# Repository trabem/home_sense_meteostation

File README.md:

# Автономна метеостанція на ESP32-C3

Репозиторій автономної battery-powered метеостанції на **ESP32-C3-WROOM-02**.
Містить firmware (ESP-IDF / FreeRTOS), KiCad-проєкти двох плат і матеріали
фінальної презентації.

Принцип роботи на battery: **wake → визначити причину → прочитати потрібні
дані → передати → перевести периферію в low-power → deep sleep**.

## Що вимірює і передає

- температура, тиск, вологість — **BME280**;
- напруга, струм, потужність battery і solar — **INA226 ×2**;
- час — RTC **DS3231** (CR2032 backup);
- стан зарядки (TP5000) і вибір транспорту — **PCA9536**;
- події блискавки — **AS3935** через `WAKE_IRQ` з негайною передачею
  distance/energy.

Транспорт вибирається перемикачем **J4**:

| J4 | Режим |
| -- | ----- |
| open / HIGH | **LoRa** (SX1262 / E22-900M22S, TX-only, компактний binary payload) — energy-safe default |
| closed / LOW | **Wi-Fi + MQTT** (JSON, `mqtts://`, BLE provisioning за відсутності credentials) |

Підключення USB автоматично вмикає continuous mode — цикли за таймером без
deep sleep, порт лишається живим для прошивки й монітору.

## Структура репозиторію

```text
software/       firmware: C11+, ESP-IDF v6.0.1, FreeRTOS, target esp32c3
  main/         composition root (app_main, flows, app_config)
  components/   board, app_flow, power_manager, sensor_manager,
                lightning_service, драйвери (bme280, as3935, ina226, ds3231,
                pca9536, sx1262), transport (MQTT/LoRa), telemetry, ...
  docs/         Mermaid-діаграми call flow і модулів
hardware/
  main_board/   KiCad-проєкт основної плати (MCU, LoRa, power: USB/Solar/1S LiFePO4)
  sensor_board/ KiCad-проєкт плати датчиків (BME280 + CJMCU-3935/AS3935)
presentation/   фінальна презентація (PDF/PPTX) і генератор
AGENTS.md       правила проєкту для AI-агентів і контрибуторів
TZ.md           історичне implementation specification
```

## Швидкий старт (firmware)

Потрібне activated ESP-IDF **v6.0.1** environment (`IDF_PATH`, `idf.py`):

```bash
cd software
idf.py set-target esp32c3   # тільки для clean setup
idf.py menuconfig           # меню "Meteostation"
idf.py build
idf.py -p PORT flash
idf.py -p PORT monitor
```

Деталі — у [`software/README.md`](software/README.md): pin mapping, I2C
addresses, MQTT/LoRa конфігурація, BLE provisioning, deep sleep і power
behavior.

## Hardware

Два KiCad-проєкти (generator_version 10.0):

- **main_board** — ESP32-C3, E22-900M22S (SX1262), power mux TPS2121
  (USB-over-Solar priority), зарядний контролер TP5000 для 1S LiFePO4,
  buck-boost 3.3 V, INA226 ×2, DS3231, PCA9536;
- **sensor_board** — BME280 (0x76) + AS3935 (0x03), підключення до основної
  плати через I²C і `WAKE_IRQ`.

Очікувані I2C addresses: `0x40` solar INA226, `0x41` PCA9536, `0x44` battery
INA226, `0x68` DS3231, `0x03` AS3935, `0x76` BME280.

## Поза скоупом V1

OTA, HTTP/web UI, LoRaWAN/RX/ACK, persistent telemetry queue, FRAM, SD card,
backend, remote configuration — навмисно не реалізовані.

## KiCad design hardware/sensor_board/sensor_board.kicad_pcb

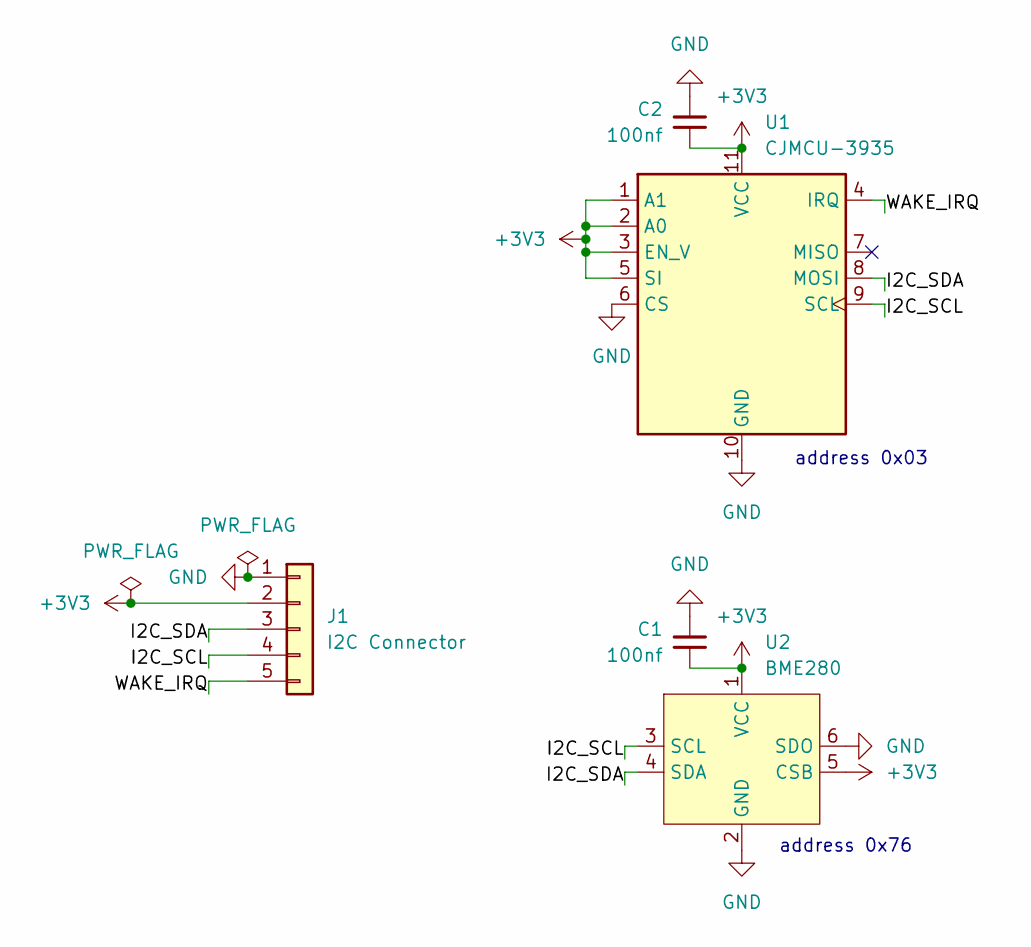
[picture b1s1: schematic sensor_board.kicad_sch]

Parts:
C1, C2: 100nf; C_Disc_D5.0mm_W2.5mm_P2.50mm
J1: I2C Connector; JST_PH_B5B-PH-K_1x05_P2.00mm_Vertical
U1: CJMCU-3935
U2: BME280; BME280 Module

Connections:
+3V3: C1.2, C2.2, J1.2, U1.1 (A1), U1.2 (A0), U1.3 (EN_V), U1.5 (SI), U1.11 (VCC), U2.1 (VCC), U2.5 (CSB)
/I2C_SCL: J1.4, U1.9 (SCL), U2.3 (SCL)
/I2C_SDA: J1.3, U1.8 (MOSI), U2.4 (SDA)
/WAKE_IRQ: J1.5, U1.4 (IRQ)
GND: C1.1, C2.1, J1.1, U1.6 (CS), U1.10 (GND), U2.2 (GND), U2.6 (SDO)

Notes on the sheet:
address 0x76
address 0x03

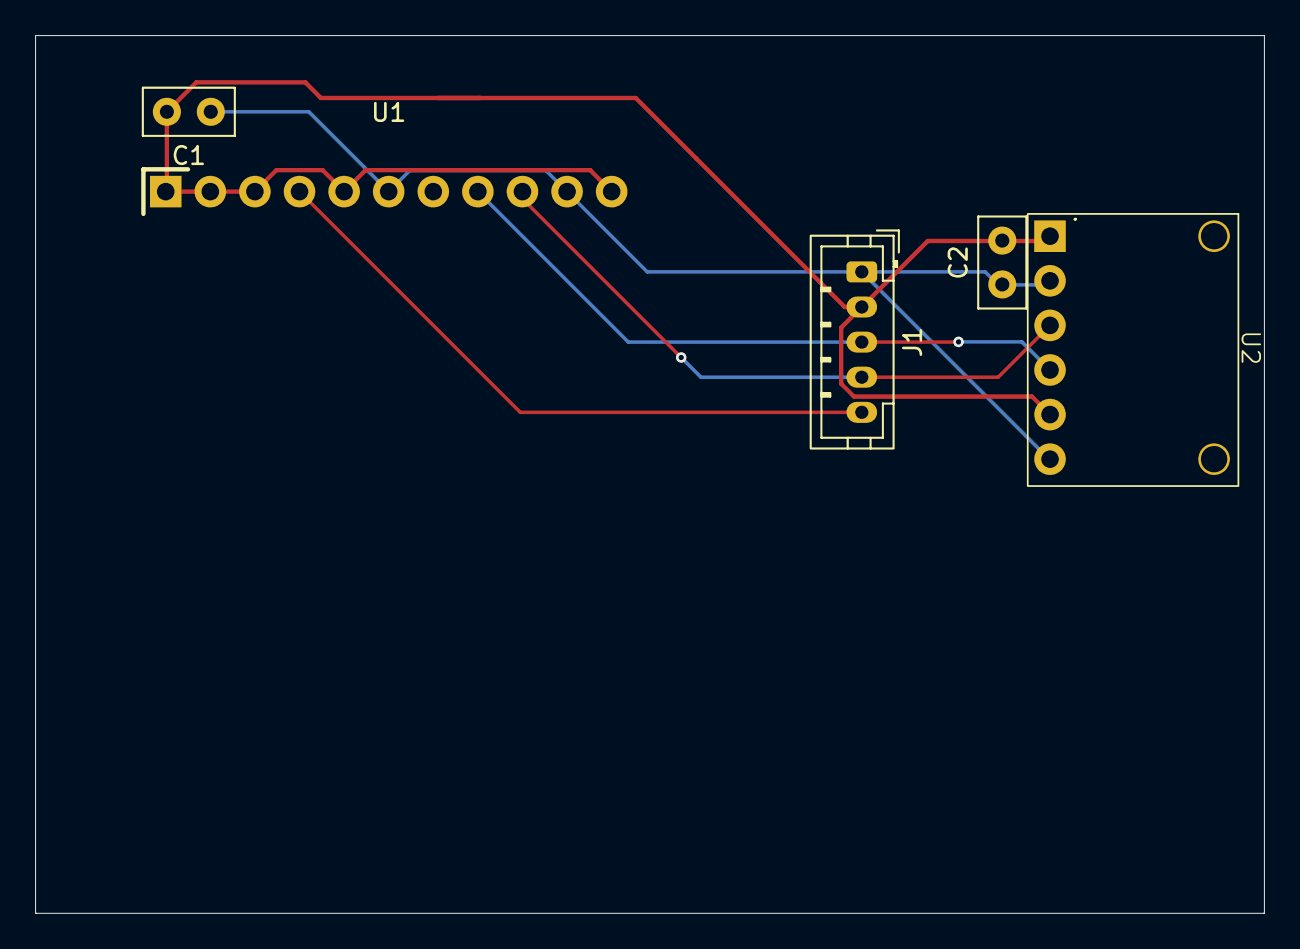
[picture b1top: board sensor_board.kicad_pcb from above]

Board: 2 copper layers, 70.0 x 50.0 mm, 5 parts (0 on the bottom side), 5 nets.

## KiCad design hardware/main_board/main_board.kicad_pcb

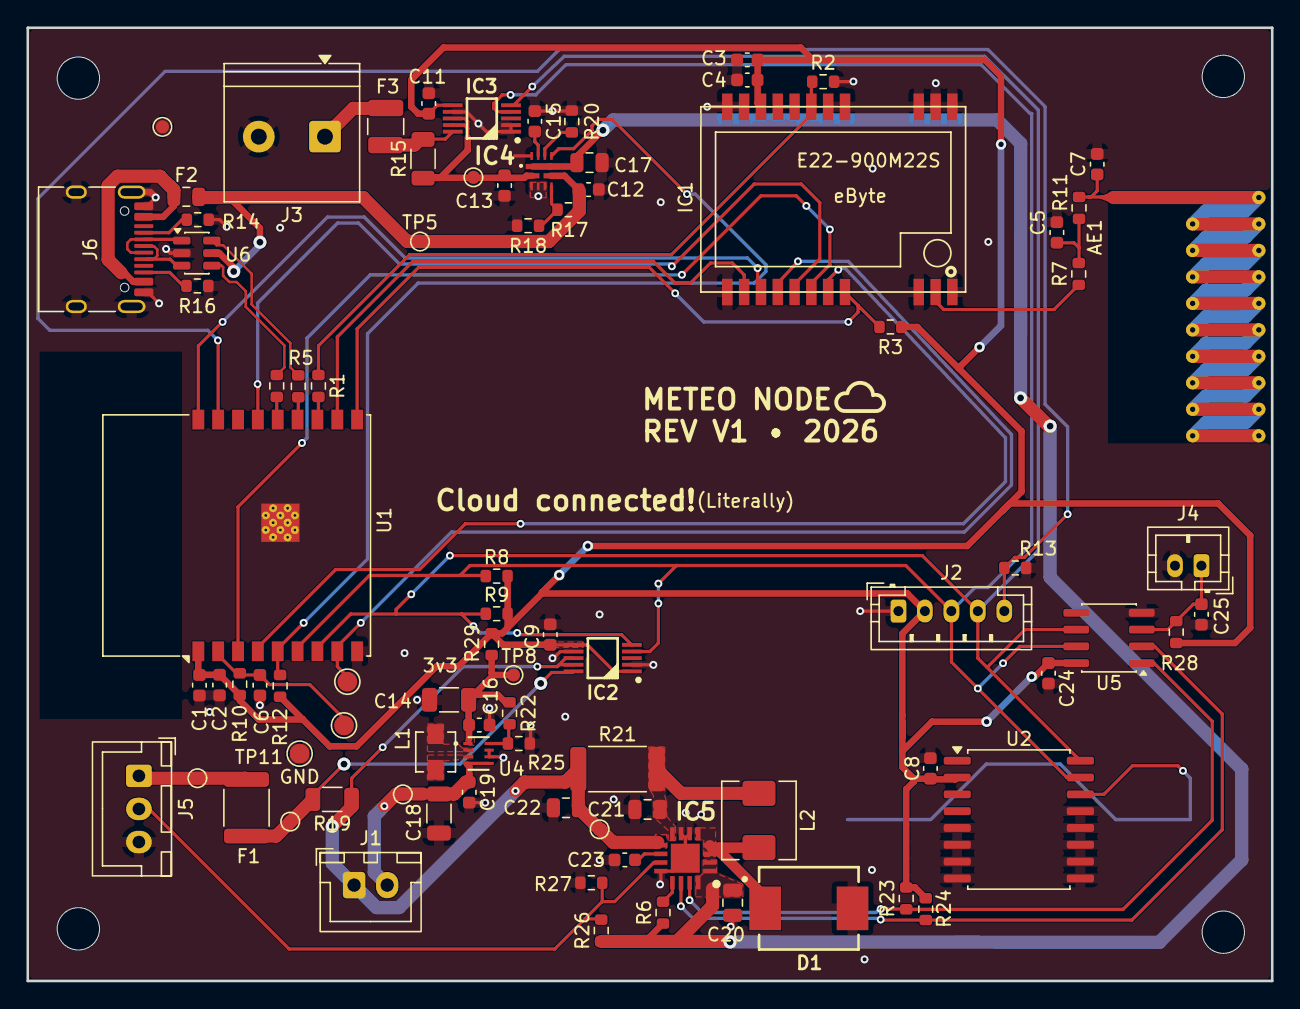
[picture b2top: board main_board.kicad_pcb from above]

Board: 2 copper layers, 94.0 x 72.0 mm, 92 parts (1 on the bottom side), 54 nets.

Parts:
AE1: Antenna; Texas_SWRA416_868MHz_915MHz
BT1: CR2032; BatteryHolder_Multicomp_BC-2001_1x2032
C1, C4: 10uF; C_0603_1608Metric
C2, C3, C8, C9, C11, C15, C16, C19, C23, C24, C25: 100nF; C_0603_1608Metric
C5, C7: DNP; C_0603_1608Metric
C6, C12, C13: 1uF; C_0603_1608Metric
C14: 47uF; C_1206_3216Metric
C17: 4.7uF; C_0805_2012Metric
C18: 22uF; C_1206_3216Metric
C20, C21, C22: 10uF; C_0805_2012Metric
D1: SS34; DO-214AB
F1: MINISMDC200F-2; Fuse_1812_4532Metric
F2: 0ZCK0075FF2E; Fuse_0805_2012Metric
F3: 0ZCH0075AF2E; Fuse_1210_3225Metric
IC1: E22-900M22S
IC2, IC3: INA226AIDGST; SOP50P490X110-10N
IC4: TPS2121RUXT
IC5: TP5000-QFN16; QFN65P400X400X90-17N-D
J1: power swith; JST_XH_B2B-XH-A_1x02_P2.50mm_Vertical
J2: I2C External Modules; JST_PH_B5B-PH-K_1x05_P2.00mm_Vertical
J3: Solar panel; TerminalBlock_Philmore_TB132_1x02_P5.00mm_Horizontal
J4: WI-FI switch; JST_PH_B2B-PH-K_1x02_P2.00mm_Vertical
J5: Battary over BMS; JST_XH_B3B-XH-A_1x03_P2.50mm_Vertical
J6: USB4105-GF-A-060; USB_C_Receptacle_HRO_TYPE-C-31-M-12
L1: IHLP1212BZER1R0M11; IND_IHLP1212BZER1R0M11
L2: 4.7 uH; L_Chilisin_BMRA00050520
R1, R6, R7, R11, R29: 0R; R_0603_1608Metric
R2, R3, R10, R12, R23, R24: 10k; R_0603_1608Metric
R4, R5: 22R; R_0603_1608Metric
R8, R9: 4.7k; R_0603_1608Metric
R13, R18, R28: 47k; R_0603_1608Metric
R14, R16: 5.1k; R_0603_1608Metric
R15, R19: 20mR; R_1206_3216Metric
R17: 150k; R_0603_1608Metric
R20: 80k; R_0603_1608Metric
R21: 330mR; R_2512_6332Metric
R22: 511k; R_0603_1608Metric
R25: 91k; R_0603_1608Metric
R26: 4.87k; R_0603_1608Metric
R27: 44.2k; R_0603_1608Metric
REF1, REF2, REF3, REF4: MountingHole_3.2mm_M3
TP1: TP_SOLAR_IN; TestPoint_Pad_D1.0mm
TP2: TP_BAT_RAW; TestPoint_Pad_D1.0mm
TP3: TP_BAT_FUSED; TestPoint_Pad_D1.0mm
TP4: TP_BAT_SYSTEM; TestPoint_Pad_D1.0mm
TP5: TP_USB_5V; TestPoint_Pad_D1.0mm
TP6: ESP32_EN; TestPoint_Pad_D1.5mm
TP7: TP_BAT_SW; TestPoint_Pad_D1.0mm
TP8: TP_3V3; TestPoint_Pad_D1.0mm
TP9: TP_GND_PWR; TestPoint_Pad_D1.0mm
TP10: ESP32_BOOT; TestPoint_Pad_D1.5mm
TP11: GND; TestPoint_Pad_D1.5mm
U1: ESP32-C3-WROOM-02
U2: DS3231SN; SOIC-16W_7.5x10.3mm_P1.27mm
U4: TPS631000DRLR; TPS631000DRLR_TEX
U5: PCA9536DR; SOIC-8_3.9x4.9mm_P1.27mm
U6: USBLC6-2SC6; SOT-23-6

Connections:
+3V3: C1.1, C2.1, C3.2, C4.1, C8.2, C9.2, C11.2, C24.1, IC1.9 (VCC), IC2.1 (A1), IC2.6 (VS+), IC3.6 (VS+), J2.2, R3.2, R8.2, R9.2, R10.1, R12.2, R23.2, R24.2, R28.1, R29.2, U1.1 (3V3), U2.2 (VCC), U5.8 (VDD)
/Power/BAT_RAW: F1.1, J5.1, TP2.1 (1_1)
/Power/CHARGER_IN: C17.2, C20.1, IC4.1 (OUT_1), IC4.8 (OUT_2), IC5.1 (VIN_1), IC5.2 (VIN_2), IC5.16 (VIN_3), R6.1, R26.1
/Power/LX_SW: D1.1 (K), IC5.3 (LX_1), IC5.4 (LX_2), IC5.5 (LX_3), L2.1
/Power/NTC_SENSE: IC5.11 (TS), J5.2, R26.2, R27.1
/Power/USB_5V: C12.2, F2.2, IC4.7 (IN1), R17.2, TP5.1 (1_1), U6.5 (VBUS)
/main_board/I2C_SCL: IC2.5 (SCL), IC3.5 (SCL), J2.4, R9.1, U1.7 (IO8), U2.16 (SCL), U5.6 (SCL)
/main_board/I2C_SDA: IC2.4 (SDA), IC3.4 (SDA), J2.3, R8.1, U1.6 (IO7), U2.15 (SDA), U5.7 (SDA)
/main_board/LORA_BUSY: IC1.14 (BUSY), U1.18 (IO0)
/main_board/LORA_DIO1: IC1.13 (DIO1), U1.11 (IO20/RXD)
/main_board/LORA_NRST: IC1.15 (NRST), TP10.1 (1_1), U1.8 (IO9)
/main_board/LORA_NSS: IC1.19 (NSS), R3.1, U1.10 (IO10)
/main_board/LORA_RXEN: IC1.6 (RXEN), R1.1, R2.1
/main_board/LORA_TXEN: IC1.7 (TXEN), IC1.8 (DIO2)
/main_board/SPI_MISO: IC1.16 (MISO), U1.15 (IO3)
/main_board/SPI_MOSI: IC1.17 (MOSI), U1.3 (IO4)
/main_board/SPI_SCK: IC1.18 (SCK), U1.4 (IO5)
/main_board/WAKE_IRQ: J2.5, R13.1, U1.17 (IO1)
/main_board/WIFI_SW: C25.2, J4.1, R28.2, U5.3 (IO2)
BAT_FUSED: F1.2, IC2.10 (VIN+), R19.2, TP3.1 (1_1)
BAT_SW: C22.1, IC2.8 (VBUS), IC2.9 (VIN-), IC5.9 (BAT), J1.1, R19.1, R21.1, TP7.1 (1_1)
BAT_SYSTEM: C18.1, C19.1, J1.2, TP4.1 (1_1), U4.4 (VIN), U4.5 (EN)
BT_CR2032: BT1.1 (+), U2.14 (VBAT)
CHARGE_SOURCE_STATUS_OUT: IC4.9 (ST), R12.1, U1.5 (IO6)
CHRG_STATUS: IC5.15 (~CHRG), R23.1, U5.1 (IO0)
GND: BT1.2 (-), C1.2, C2.2, C3.1, C4.2, C5.2, C6.2, C7.2, C8.1, C9.1, C11.1, C12.1, C13.1, C14.2, C15.1, C16.2, C17.1, C18.2, C19.2, C20.2, C21.2, C22.2, C23.2, C24.2, C25.1, D1.2 (A), IC1.1 (GND), IC1.2 (GND), IC1.3 (GND), IC1.4 (GND), IC1.5 (GND), IC1.10 (GND), IC1.11 (GND), IC1.12 (GND), IC1.20 (GND), IC1.22 (GND), IC2.2 (A0), IC2.7 (GND), IC3.1 (A1), IC3.2 (A0), IC3.7 (GND), IC4.3 (CP2), IC4.4 (OV2), IC4.5 (OV1), IC4.12 (GND), IC5.6 (GND_1), IC5.7 (GND_2), IC5.12 (RTRICK), IC5.17 (EP), J2.1, J3.2, J4.2, J5.3, J6.A1 (GND), J6.A12 (GND), J6.B1 (GND), J6.B12 (GND), J6.SH (SHIELD), R2.2, R13.2, R14.1, R16.2, R18.1, R20.2, R25.2, R27.2, TP9.1 (1_1), TP11.1 (1_1), U1.9 (GND), U1.19 (GND), U2.5 (GND), U2.6 (GND), U2.7 (GND), U2.8 (GND), U2.9 (GND), U2.10 (GND), U2.11 (GND), U2.12 (GND), U2.13 (GND), U4.6 (MODE), U4.7 (GND), U5.4 (VSS), U6.2 (GND)
unnamed: AE1.1 (A_1), C7.1, R11.2
unnamed: C5.1, R7.2, R11.1
unnamed: F2.1, J6.A4 (VBUS), J6.A9 (VBUS), J6.B4 (VBUS), J6.B9 (VBUS)
unnamed: IC1.21 (ANT), R7.1
unnamed: IC4.10 (ILIM), R20.1
unnamed: IC4.6 (PR1), R17.1, R18.2
unnamed: C15.2, IC4.11 (SS)
unnamed: IC5.13 (CS), R6.2
unnamed: C23.1, IC5.10 (VREG)
unnamed: C21.1, IC5.8 (VS), L2.2, R21.2
unnamed: F3.1, J3.1
unnamed: J6.A5 (CC1), R14.2
unnamed: J6.B5 (CC2), R16.1
unnamed: J6.A6 (D+), J6.B6 (D+), U6.3 (I/O2)
unnamed: J6.A7 (D-), J6.B7 (D-), U6.1 (I/O1)
unnamed: C6.1, R10.2, TP6.1 (1_1), U1.2 (EN)
unnamed: R5.1, U1.13 (IO18)
unnamed: R4.2, U1.14 (IO19)
unnamed: R1.2, U1.12 (IO21/TXD)
unnamed: R22.2, R25.1, U4.8 (FB)
unnamed: L1.1, U4.3 (LX1)
unnamed: L1.2, U4.2 (LX2)
unnamed: C14.1, C16.1, R22.1, R29.1, TP8.1 (1_1), U4.1 (VOUT)
SOLAR+: F3.2, IC3.10 (VIN+), R15.2
SOLAR_IN: C13.2, IC3.8 (VBUS), IC3.9 (VIN-), IC4.2 (IN2), R15.1, TP1.1 (1_1)
STDBY_STATUS: IC5.14 (~STDBY), R24.1, U5.2 (IO1)
USB_D+: R4.1, U6.4 (I/O2)
USB_D-: R5.2, U6.6 (I/O1)
